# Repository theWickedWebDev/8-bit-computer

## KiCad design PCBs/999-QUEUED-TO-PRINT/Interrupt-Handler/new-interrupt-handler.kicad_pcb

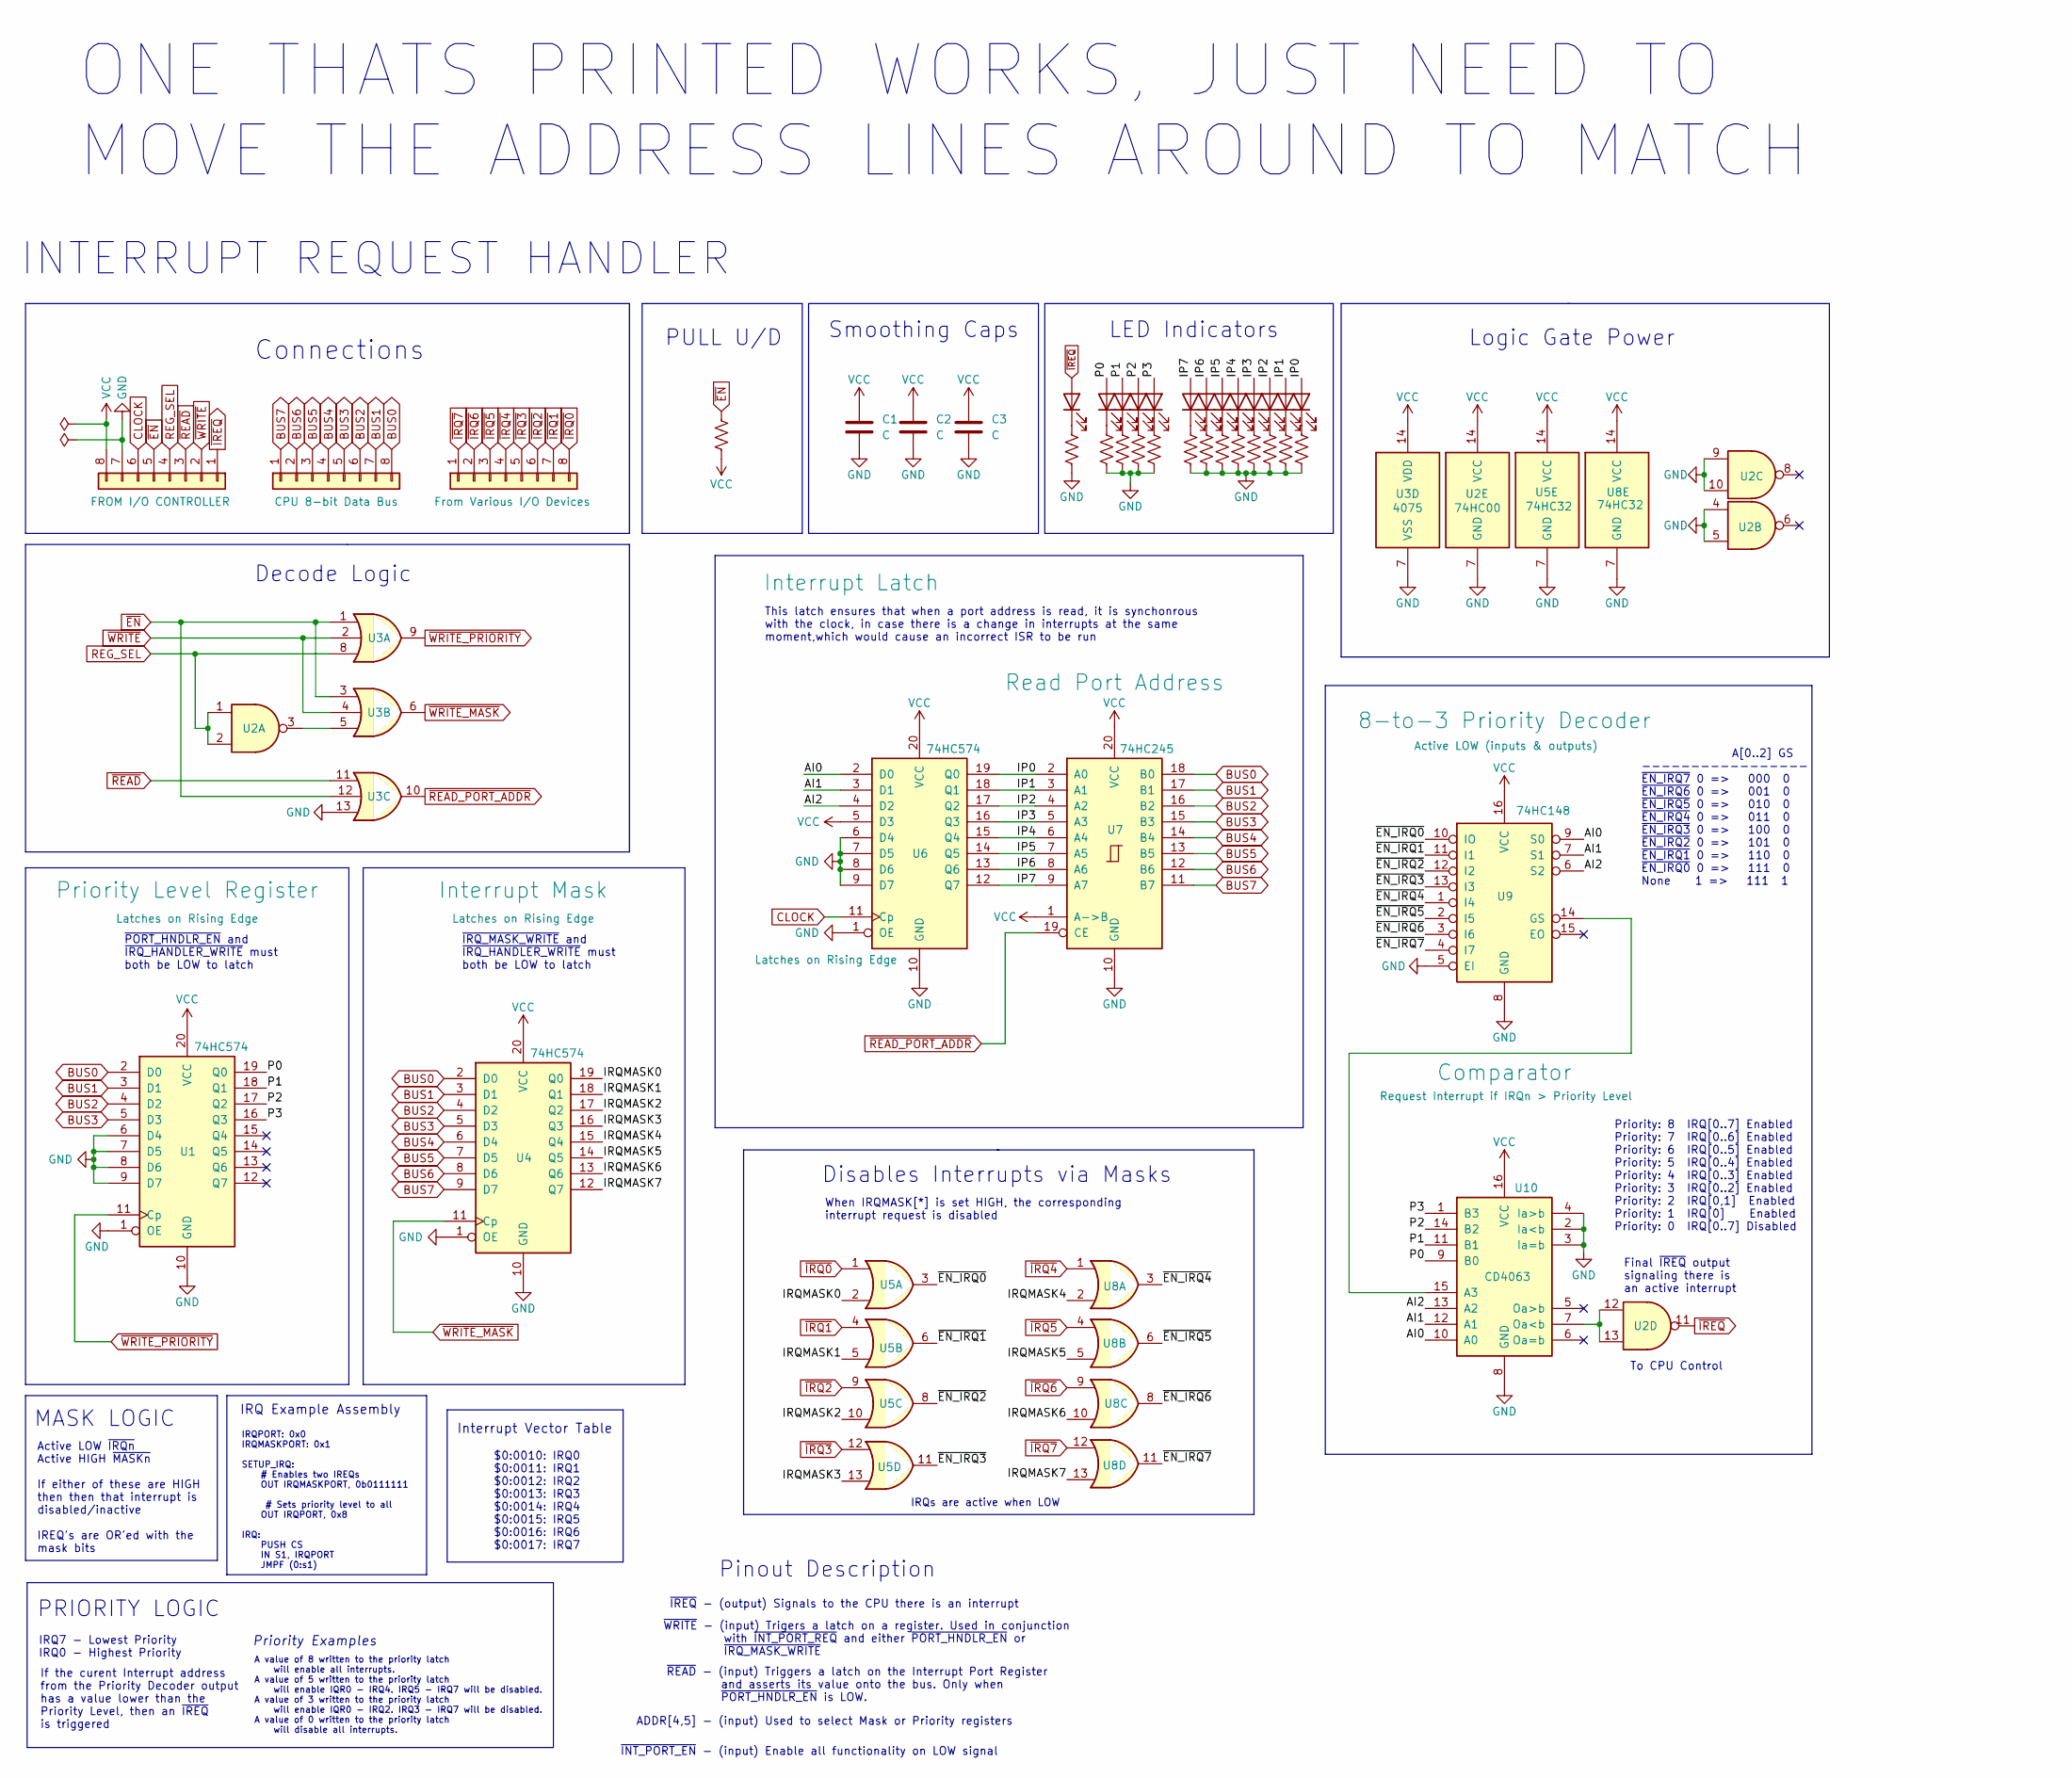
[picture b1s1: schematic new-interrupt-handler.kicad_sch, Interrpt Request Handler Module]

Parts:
C1, C2, C3: C; C_0805_2012Metric
D1, D2, D3, D4, D5, D6, D7, D8, D9, D10, D11, D12, D13: LED; LED_0805_2012Metric
J1, J2, J3: Conn_01x08; PinHeader_1x08_P2.54mm_Vertical
R1, R2, R3, R4, R5, R6, R7, R8, R9, R10, R11, R12, R13, R14: R_US; R_0805_2012Metric
U1, U4, U6: 74HC574; SO-20_5.3x12.6mm_P1.27mm
U2: 74HC00; TSSOP-14_4.4x5mm_P0.65mm
U3: 4075
U5, U8: 74HC32; TSSOP-14_4.4x5mm_P0.65mm
U7: 74HC245; TSSOP-20_4.4x6.5mm_P0.65mm
U9: 74HC148; SOIC-16_4.55x10.3mm_P1.27mm
U10: CD4063; SO-16_5.3x10.2mm_P1.27mm

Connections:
/AI0: U6.2 (D0), U9.9 (S0), U10.10 (A0)
/AI1: U6.3 (D1), U9.7 (S1), U10.12 (A1)
/AI2: U6.4 (D2), U9.6 (S2), U10.13 (A2)
/IP0: D13.2 (A), U6.19 (Q0), U7.2 (A0)
/IP1: D12.2 (A), U6.18 (Q1), U7.3 (A1)
/IP2: D11.2 (A), U6.17 (Q2), U7.4 (A2)
/IP3: D10.2 (A), U6.16 (Q3), U7.5 (A3)
/IP4: D9.2 (A), U6.15 (Q4), U7.6 (A4)
/IP5: D8.2 (A), U6.14 (Q5), U7.7 (A5)
/IP6: D7.2 (A), U6.13 (Q6), U7.8 (A6)
/IP7: D6.2 (A), U6.12 (Q7), U7.9 (A7)
/IRQMASK0: U4.19 (Q0), U5.2
/IRQMASK1: U4.18 (Q1), U5.5
/IRQMASK2: U4.17 (Q2), U5.10
/IRQMASK3: U4.16 (Q3), U5.13
/IRQMASK4: U4.15 (Q4), U8.2
/IRQMASK5: U4.14 (Q5), U8.5
/IRQMASK6: U4.13 (Q6), U8.10
/IRQMASK7: U4.12 (Q7), U8.13
/P0: D2.2 (A), U1.19 (Q0), U10.9 (B0)
/P1: D3.2 (A), U1.18 (Q1), U10.11 (B1)
/P2: D4.2 (A), U1.17 (Q2), U10.14 (B2)
/P3: D5.2 (A), U1.16 (Q3), U10.1 (B3)
/~EN_IRQ0: U5.3, U9.10 (IO)
/~EN_IRQ1: U5.6, U9.11 (I1)
/~EN_IRQ2: U5.8, U9.12 (I2)
/~EN_IRQ3: U5.11, U9.13 (I3)
/~EN_IRQ4: U8.3, U9.1 (I4)
/~EN_IRQ5: U8.6, U9.2 (I5)
/~EN_IRQ6: U8.8, U9.3 (I6)
/~EN_IRQ7: U8.11, U9.4 (I7)
BUS0: J2.8, U1.2 (D0), U4.2 (D0), U7.18 (B0)
BUS1: J2.7, U1.3 (D1), U4.3 (D1), U7.17 (B1)
BUS2: J2.6, U1.4 (D2), U4.4 (D2), U7.16 (B2)
BUS3: J2.5, U1.5 (D3), U4.5 (D3), U7.15 (B3)
BUS4: J2.4, U4.6 (D4), U7.14 (B4)
BUS5: J2.3, U4.7 (D5), U7.13 (B5)
BUS6: J2.2, U4.8 (D6), U7.12 (B6)
BUS7: J2.1, U4.9 (D7), U7.11 (B7)
CLOCK: J1.6, U6.11 (Cp)
GND: C1.2, C2.2, C3.2, J1.7, R2.2, R3.2, R4.2, R5.2, R6.2, R7.2, R8.2, R9.2, R10.2, R11.2, R12.2, R13.2, R14.2, U1.1 (OE), U1.6 (D4), U1.7 (D5), U1.8 (D6), U1.9 (D7), U1.10 (GND), U2.4, U2.5, U2.7 (GND), U2.9, U2.10, U3.7 (VSS), U3.13, U4.1 (OE), U4.10 (GND), U5.7 (GND), U6.1 (OE), U6.6 (D4), U6.7 (D5), U6.8 (D6), U6.9 (D7), U6.10 (GND), U7.10 (GND), U8.7 (GND), U9.5 (EI), U9.8 (GND), U10.2 (Ia<b), U10.3 (Ia=b), U10.4 (Ia>b), U10.8 (GND)
unnamed: D1.1 (K), R2.1
unnamed: D2.1 (K), R3.1
unnamed: D3.1 (K), R4.1
unnamed: D4.1 (K), R5.1
unnamed: D5.1 (K), R6.1
unnamed: D6.1 (K), R7.1
unnamed: D7.1 (K), R8.1
unnamed: D8.1 (K), R9.1
unnamed: D9.1 (K), R10.1
unnamed: D10.1 (K), R11.1
unnamed: D11.1 (K), R12.1
unnamed: D12.1 (K), R13.1
unnamed: D13.1 (K), R14.1
unnamed: U2.3, U3.5
unnamed: U2.12, U2.13, U10.7 (Oa<b)
unnamed: U9.14 (GS), U10.15 (A3)
REG_SEL: J1.4, U2.1, U2.2, U3.8
VCC: C1.1, C2.1, C3.1, J1.8, R1.2, U1.20 (VCC), U2.14 (VCC), U3.14 (VDD), U4.20 (VCC), U5.14 (VCC), U6.5 (D3), U6.20 (VCC), U7.1 (A->B), U7.20 (VCC), U8.14 (VCC), U9.16 (VCC), U10.16 (VCC)
~EN: J1.5, R1.1, U3.1, U3.3, U3.12
~IREQ: D1.2 (A), J1.1, U2.11
~IRQ0: J3.8, U5.1
~IRQ1: J3.7, U5.4
~IRQ2: J3.6, U5.9
~IRQ3: J3.5, U5.12
~IRQ4: J3.4, U8.1
~IRQ5: J3.3, U8.4
~IRQ6: J3.2, U8.9
~IRQ7: J3.1, U8.12
~READ_PORT_ADDR: U3.10, U7.19 (CE)
~READ: J1.3, U3.11
~WRITE_MASK: U3.6, U4.11 (Cp)
~WRITE_PRIORITY: U1.11 (Cp), U3.9
~WRITE: J1.2, U3.2, U3.4

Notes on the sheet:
When IRQMASK[*] is set HIGH, the corresponding interrupt request is disabled
Disables Interrupts via Masks
IRQPORT: 0x0 IRQMASKPORT: 0x1 SETUP_IRQ: # Enables two IREQs OUT IRQMASKPORT, 0b0111111 # Sets priority level to all OUT IRQPORT, 0x8 IRQ: PUSH CS IN S1, IRQPORT JMPF (0:s1)
ONE THATS PRINTED WORKS, JUST NEED TO MOVE THE ADDRESS LINES AROUND TO MATCH
~{IRQ_MASK_WRITE} and ~{IRQ_HANDLER_WRITE} must both be LOW to latch
A[0..2] GS ----------------- ~{EN_IRQ7} 0 => 000 0 ~{EN_IRQ6} 0 => 001 0 ~{EN_IRQ5} 0 => 010 0 ~{EN_IRQ4} 0 => 011 0 ~{EN_IRQ3} 0 => 100 0 ~{EN_IRQ2} 0 => 101 0 ~{EN_IRQ1} 0 => 110 0 ~{EN_IRQ0} 0 => 111 0 None 1 => 111 1
Priority: 8 IRQ[0..7] Enabled Priority: 7 IRQ[0..6] Enabled Priority: 6 IRQ[0..5] Enabled Priority: 5 IRQ[0..4] Enabled Priority: 4 IRQ[0..3] Enabled Priority: 3 IRQ[0..2] Enabled Priority: 2 IRQ[0,1] Enabled Priority: 1 IRQ[0] Enabled Priority: 0 IRQ[0..7] Disabled
INTERRUPT REQUEST HANDLER
~{INT_PORT_EN} - (input) Enable all functionality on LOW signal
Pinout Description
LED Indicators
To CPU Control
IRQs are active when LOW
PULL U/D
$0:0010: IRQ0 $0:0011: IRQ1 $0:0012: IRQ2 $0:0013: IRQ3 $0:0014: IRQ4 $0:0015: IRQ5 $0:0016: IRQ6 $0:0017: IRQ7
~{WRITE} - (input) Trigers a latch on a register. Used in conjunction with ~{INT_PORT_REQ} and either ~{PORT_HNDLR_EN} or ~{IRQ_MASK_WRITE}
Logic Gate Power
~{IREQ} - (output) Signals to the CPU there is an interrupt
IRQ7 - Lowest Priority IRQ0 - Highest Priority
If the curent Interrupt address from the Priority Decoder output has a value lower than the Priority Level, then an ~{IREQ} is triggered
A value of 8 written to the priority latch will enable all interrupts. A value of 5 written to the priority latch will enable IQR0 - IRQ4. IRQ5 - IRQ7 will be disabled. A value of 3 written to the priority latch will enable IQR0 - IRQ2. IRQ3 - IRQ7 will be disabled. A value of 0 written to the prio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
Active LOW ~{IRQn} Active HIGH ~{MASKn} If either of these are HIGH then then that interrupt is disabled/inactive IREQ's are OR'ed with the mask bits
ADDR[4,5] - (input) Used to select Mask or Priority registers
MASK LOGIC
This latch ensures that when a port address is read, it is synchonrous with the clock, in case there is a change in interrupts at the same moment,which would cause an incorrect ISR to be run
Smoothing Caps
IRQ Example Assembly
Final ~{IREQ} output signaling there is an active interrupt
Priority Examples
~{PORT_HNDLR_EN} and ~{IRQ_HANDLER_WRITE} must both be LOW to latch
PRIORITY LOGIC
Decode Logic
~{READ} - (input) Triggers a latch on the Interrupt Port Register and asserts its value onto the bus. Only when ~{PORT_HNDLR_EN} is LOW.
Connections
Interrupt Vector Table

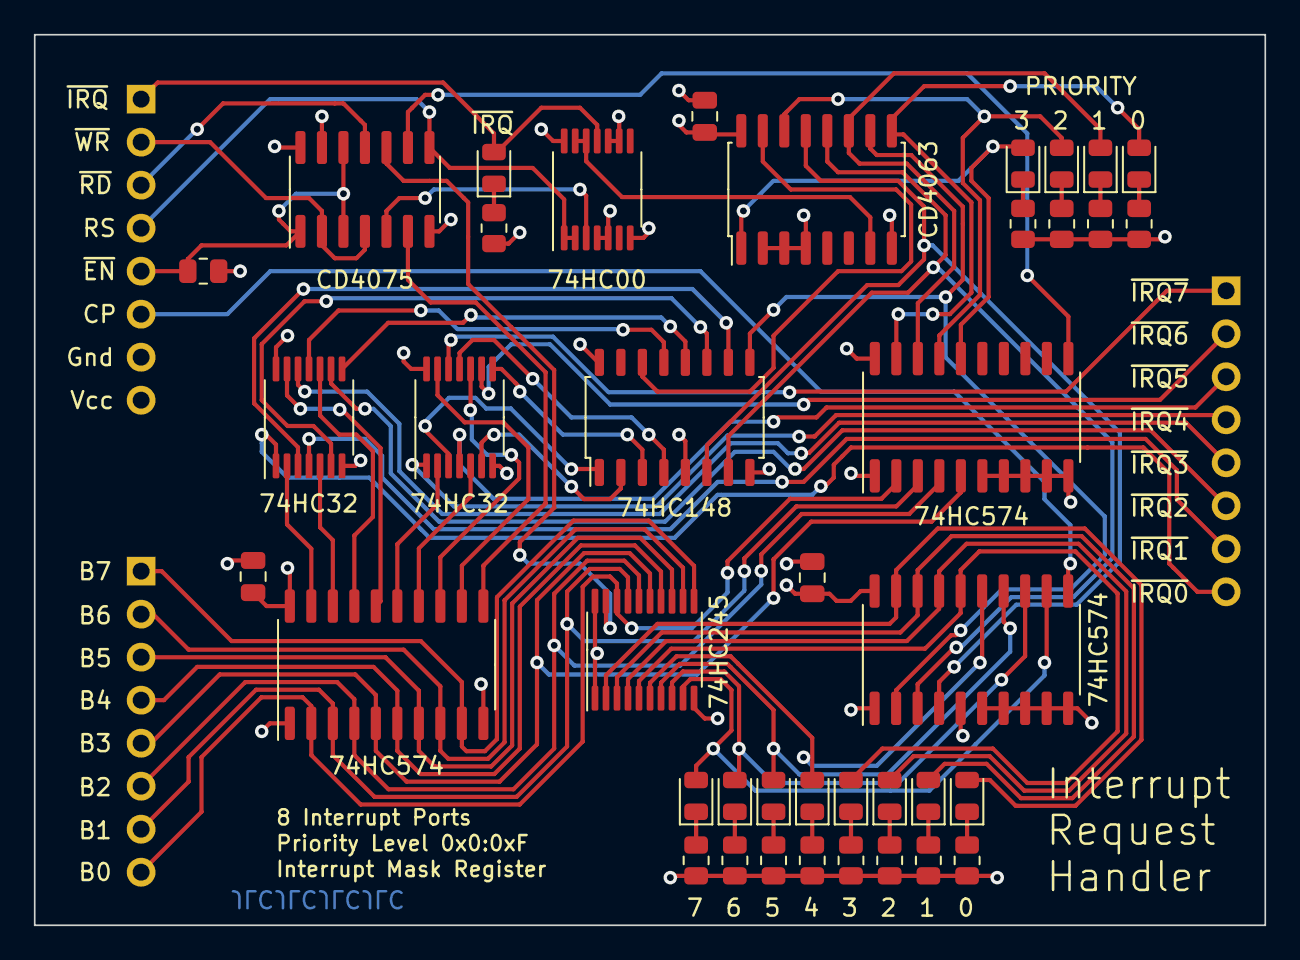
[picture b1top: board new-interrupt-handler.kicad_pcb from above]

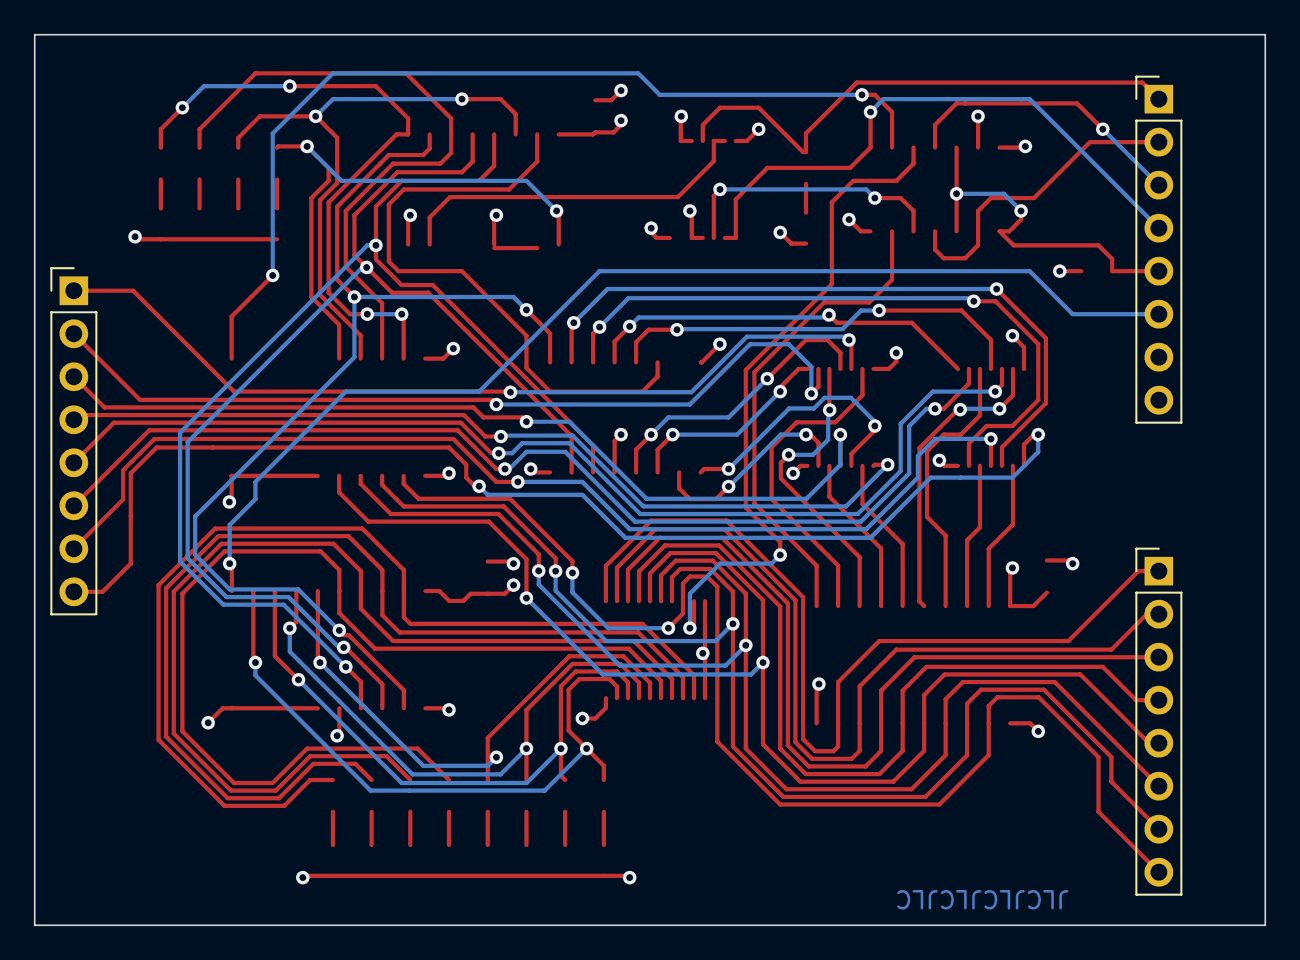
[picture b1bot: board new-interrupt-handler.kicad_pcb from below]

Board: 4 copper layers, 72.7 x 52.6 mm, 43 parts (3 on the bottom side), 74 nets.

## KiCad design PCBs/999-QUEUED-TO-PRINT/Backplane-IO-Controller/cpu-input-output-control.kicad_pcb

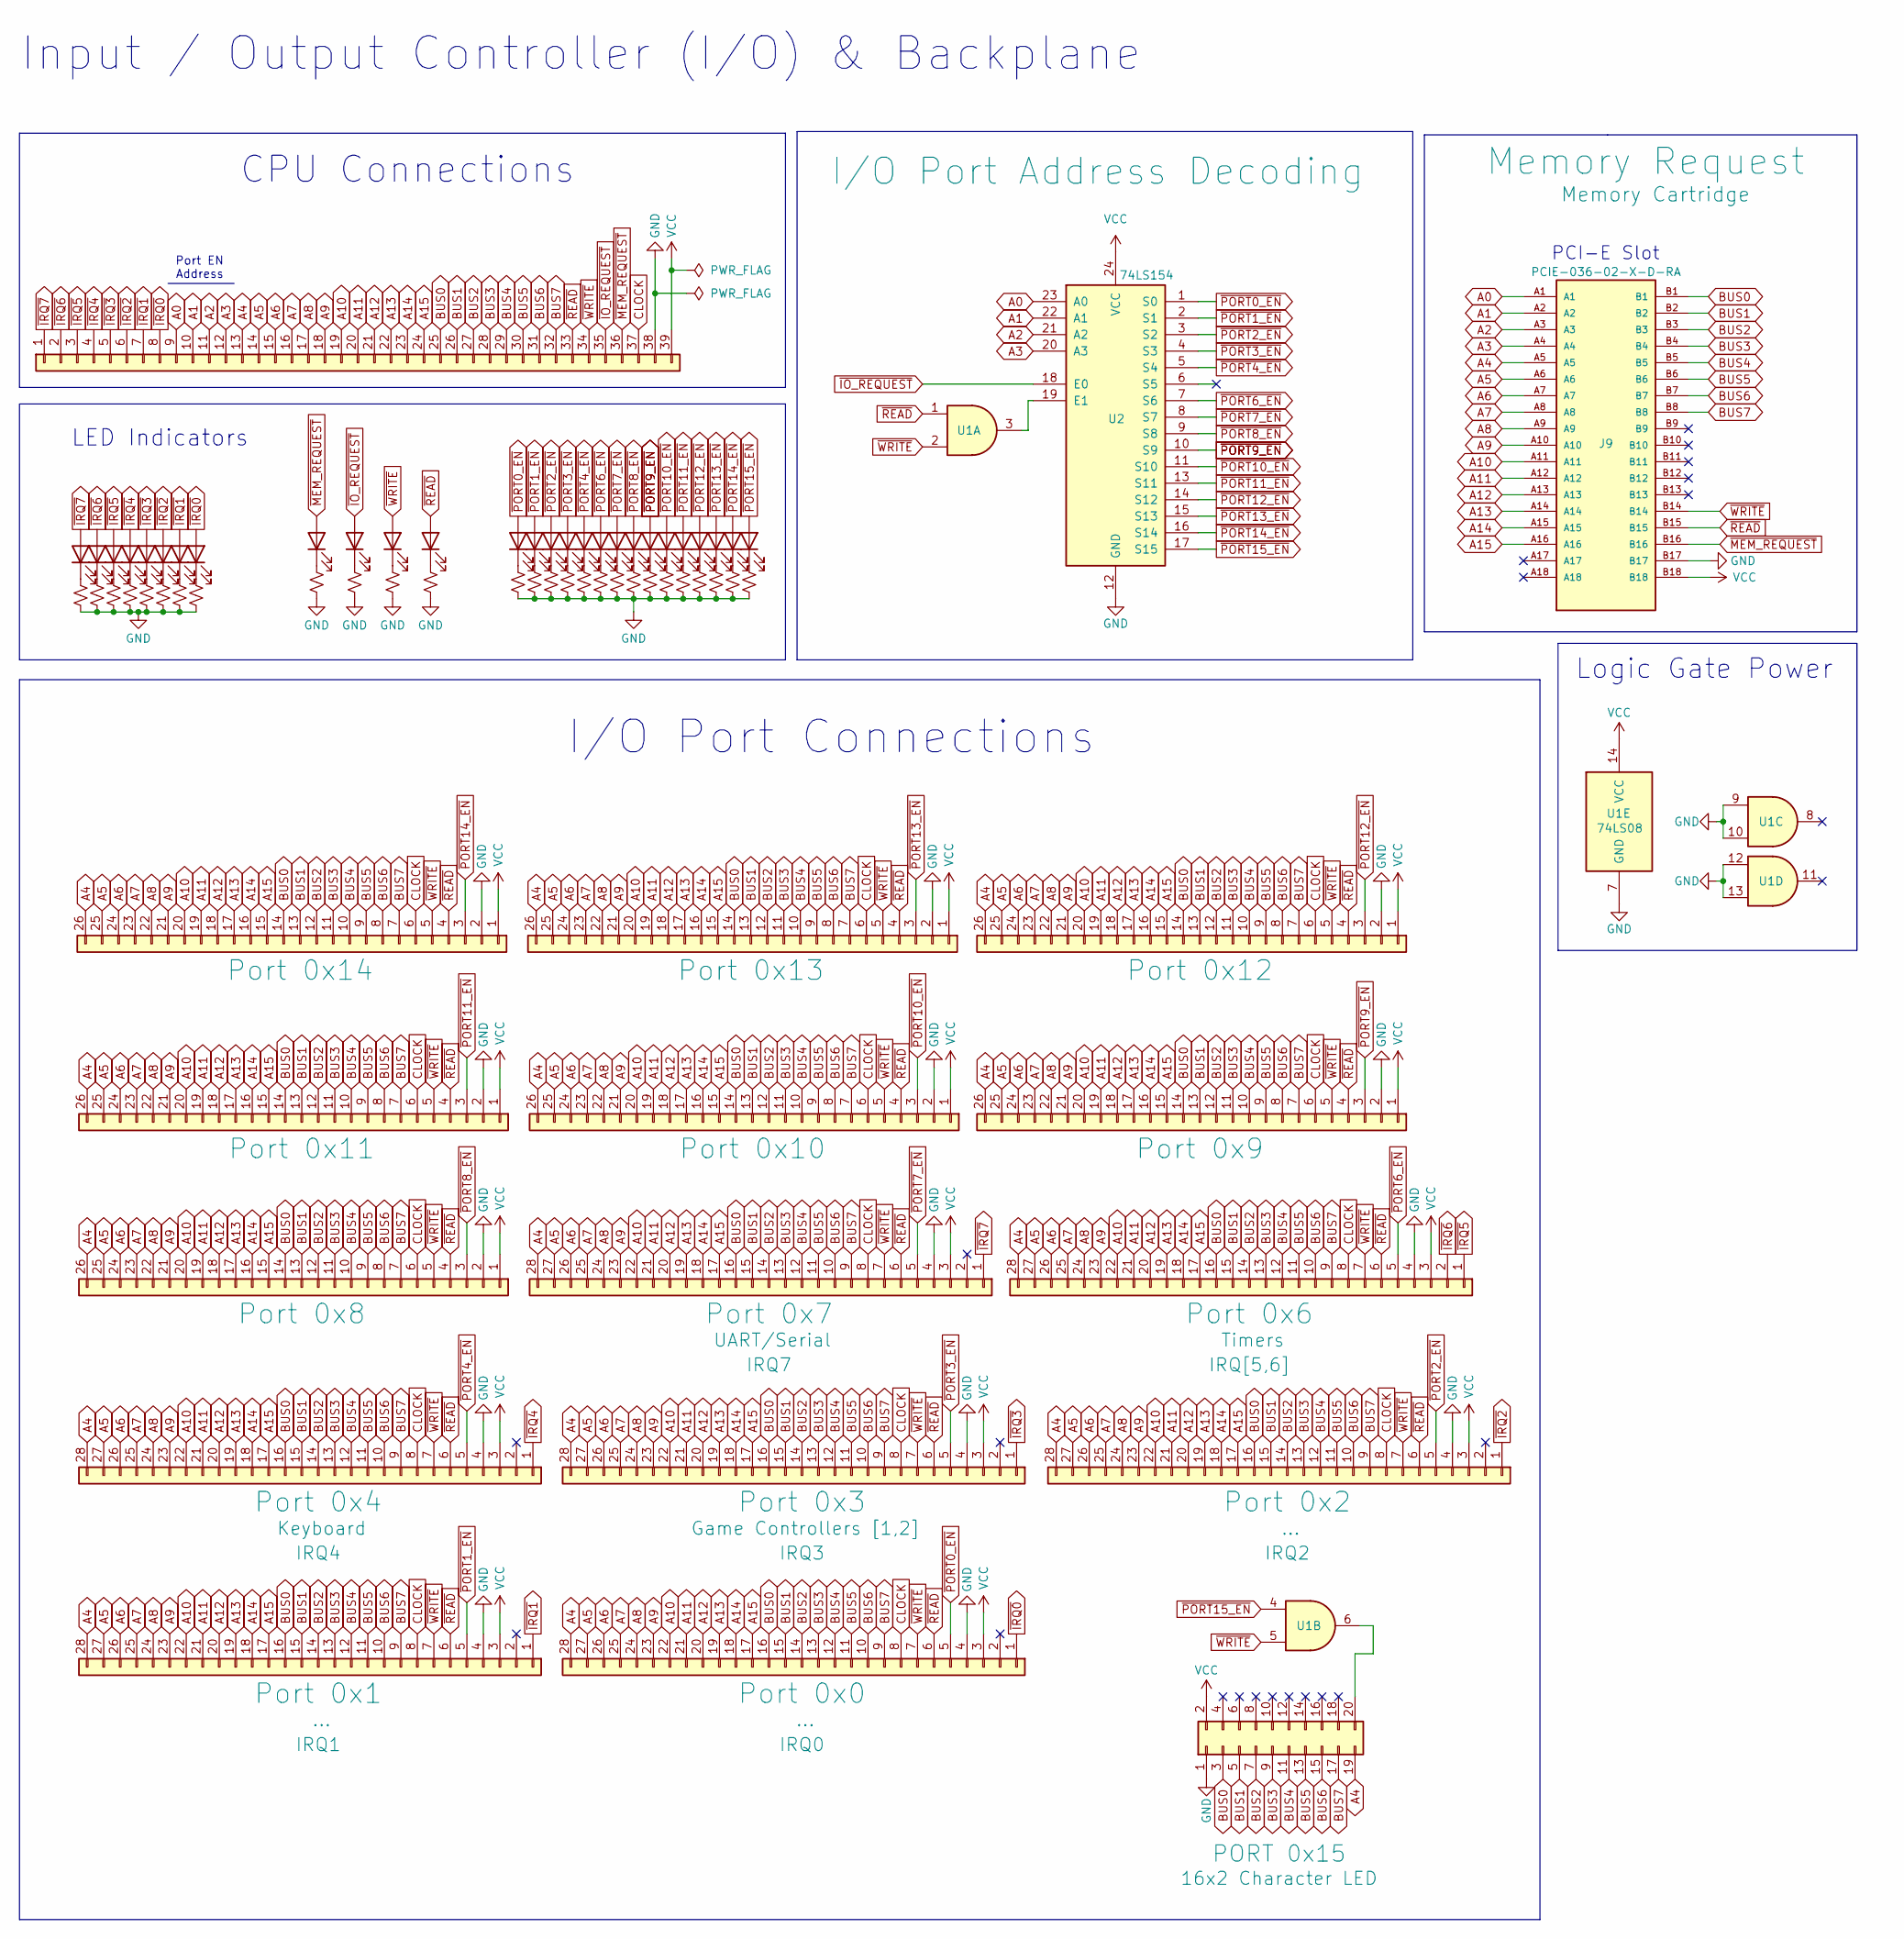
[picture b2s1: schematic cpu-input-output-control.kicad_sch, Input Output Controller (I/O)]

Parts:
D1, D2, D3, D4, D5, D6, D7, D8, D9, D10, D11, D12, D13, D14, D15, D16, D17, D18, D19, D20, D21, D22, D23, D24, D25, D26, D27: LED; LED_0805_2012Metric
J1, J4, J6, J8, J12, J14, J16: Conn_01x26; PinSocket_1x26_P2.54mm_Vertical
J2, J5, J7, J10, J13, J15, J17: Conn_01x28; PinSocket_1x28_P2.54mm_Vertical
J3: Conn_01x39; PinSocket_1x39_P2.54mm_Horizontal
J9: PCIE-036-02-X-D-RA; SAMTEC_PCIE-036-02-X-D-RA; PARTREV D
J11: Conn_02x20_Odd_Even; IDC-Header_2x10_P2.54mm_Vertical
R1, R2, R3, R4, R5, R6, R7, R8, R9, R10, R11, R12, R13, R14, R15, R16, R17, R18, R19, R20, R21, R22, R23, R24, R25, R26, R27: R_Small_US; R_0805_2012Metric
U1: 74LS08; SOIC-14_3.9x8.7mm_P1.27mm
U2: 74LS154; SO-24_5.3x15mm_P1.27mm

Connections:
A0: J3.9, J9.A1, U2.23 (A0)
A1: J3.10, J9.A2, U2.22 (A1)
A2: J3.11, J9.A3, U2.21 (A2)
A3: J3.12, J9.A4, U2.20 (A3)
A4: J1.26, J2.28, J3.13, J4.26, J5.28, J6.26, J7.28, J8.26, J9.A5, J10.28, J11.19, J12.26, J13.28, J14.26, J15.28, J16.26, J17.28
A5: J1.25, J2.27, J3.14, J4.25, J5.27, J6.25, J7.27, J8.25, J9.A6, J10.27, J12.25, J13.27, J14.25, J15.27, J16.25, J17.27
A6: J1.24, J2.26, J3.15, J4.24, J5.26, J6.24, J7.26, J8.24, J9.A7, J10.26, J12.24, J13.26, J14.24, J15.26, J16.24, J17.26
A7: J1.23, J2.25, J3.16, J4.23, J5.25, J6.23, J7.25, J8.23, J9.A8, J10.25, J12.23, J13.25, J14.23, J15.25, J16.23, J17.25
A8: J1.22, J2.24, J3.17, J4.22, J5.24, J6.22, J7.24, J8.22, J9.A9, J10.24, J12.22, J13.24, J14.22, J15.24, J16.22, J17.24
A9: J1.21, J2.23, J3.18, J4.21, J5.23, J6.21, J7.23, J8.21, J9.A10, J10.23, J12.21, J13.23, J14.21, J15.23, J16.21, J17.23
A10: J1.20, J2.22, J3.19, J4.20, J5.22, J6.20, J7.22, J8.20, J9.A11, J10.22, J12.20, J13.22, J14.20, J15.22, J16.20, J17.22
A11: J1.19, J2.21, J3.20, J4.19, J5.21, J6.19, J7.21, J8.19, J9.A12, J10.21, J12.19, J13.21, J14.19, J15.21, J16.19, J17.21
A12: J1.18, J2.20, J3.21, J4.18, J5.20, J6.18, J7.20, J8.18, J9.A13, J10.20, J12.18, J13.20, J14.18, J15.20, J16.18, J17.20
A13: J1.17, J2.19, J3.22, J4.17, J5.19, J6.17, J7.19, J8.17, J9.A14, J10.19, J12.17, J13.19, J14.17, J15.19, J16.17, J17.19
A14: J1.16, J2.18, J3.23, J4.16, J5.18, J6.16, J7.18, J8.16, J9.A15, J10.18, J12.16, J13.18, J14.16, J15.18, J16.16, J17.18
A15: J1.15, J2.17, J3.24, J4.15, J5.17, J6.15, J7.17, J8.15, J9.A16, J10.17, J12.15, J13.17, J14.15, J15.17, J16.15, J17.17
BUS0: J1.14, J2.16, J3.25, J4.14, J5.16, J6.14, J7.16, J8.14, J9.B1, J10.16, J11.3, J12.14, J13.16, J14.14, J15.16, J16.14, J17.16
BUS1: J1.13, J2.15, J3.26, J4.13, J5.15, J6.13, J7.15, J8.13, J9.B2, J10.15, J11.5, J12.13, J13.15, J14.13, J15.15, J16.13, J17.15
BUS2: J1.12, J2.14, J3.27, J4.12, J5.14, J6.12, J7.14, J8.12, J9.B3, J10.14, J11.7, J12.12, J13.14, J14.12, J15.14, J16.12, J17.14
BUS3: J1.11, J2.13, J3.28, J4.11, J5.13, J6.11, J7.13, J8.11, J9.B4, J10.13, J11.9, J12.11, J13.13, J14.11, J15.13, J16.11, J17.13
BUS4: J1.10, J2.12, J3.29, J4.10, J5.12, J6.10, J7.12, J8.10, J9.B5, J10.12, J11.11, J12.10, J13.12, J14.10, J15.12, J16.10, J17.12
BUS5: J1.9, J2.11, J3.30, J4.9, J5.11, J6.9, J7.11, J8.9, J9.B6, J10.11, J11.13, J12.9, J13.11, J14.9, J15.11, J16.9, J17.11
BUS6: J1.8, J2.10, J3.31, J4.8, J5.10, J6.8, J7.10, J8.8, J9.B7, J10.10, J11.15, J12.8, J13.10, J14.8, J15.10, J16.8, J17.10
BUS7: J1.7, J2.9, J3.32, J4.7, J5.9, J6.7, J7.9, J8.7, J9.B8, J10.9, J11.17, J12.7, J13.9, J14.7, J15.9, J16.7, J17.9
CLOCK: J1.6, J2.8, J3.37, J4.6, J5.8, J6.6, J7.8, J8.6, J10.8, J12.6, J13.8, J14.6, J15.8, J16.6, J17.8
GND: J1.2, J2.4, J3.38, J4.2, J5.4, J6.2, J7.4, J8.2, J9.B17, J10.4, J11.1, J12.2, J13.4, J14.2, J15.4, J16.2, J17.4, R1.2, R2.2, R3.2, R4.2, R5.2, R6.2, R7.2, R8.2, R9.2, R10.2, R11.2, R12.2, R13.2, R14.2, R15.2, R16.2, R17.2, R18.2, R19.2, R20.2, R21.2, R22.2, R23.2, R24.2, R25.2, R26.2, R27.2, U1.7 (GND), U1.9, U1.10, U1.12, U1.13, U2.12 (GND)
unnamed: D1.1 (K), R1.1
unnamed: D2.1 (K), R2.1
unnamed: D3.1 (K), R3.1
unnamed: D4.1 (K), R4.1
unnamed: D5.1 (K), R5.1
unnamed: D6.1 (K), R6.1
unnamed: D7.1 (K), R7.1
unnamed: D8.1 (K), R8.1
unnamed: D9.1 (K), R9.1
unnamed: D10.1 (K), R10.1
unnamed: D11.1 (K), R11.1
unnamed: D12.1 (K), R12.1
unnamed: D13.1 (K), R13.1
unnamed: D14.1 (K), R14.1
unnamed: D15.1 (K), R15.1
unnamed: D16.1 (K), R16.1
unnamed: D17.1 (K), R17.1
unnamed: D18.1 (K), R18.1
unnamed: D19.1 (K), R19.1
unnamed: D20.1 (K), R20.1
unnamed: D21.1 (K), R21.1
unnamed: D22.1 (K), R22.1
unnamed: D23.1 (K), R23.1
unnamed: D24.1 (K), R24.1
unnamed: D25.1 (K), R25.1
unnamed: D26.1 (K), R26.1
unnamed: D27.1 (K), R27.1
unnamed: J11.20, U1.6
unnamed: U1.3, U2.19 (E1)
VCC: J1.1, J2.3, J3.39, J4.1, J5.3, J6.1, J7.3, J8.1, J9.B18, J10.3, J11.2, J12.1, J13.3, J14.1, J15.3, J16.1, J17.3, U1.14 (VCC), U2.24 (VCC)
~IO_REQUEST: D10.2 (A), J3.35, U2.18 (E0)
~IRQ0: D8.2 (A), J3.8, J17.1
~IRQ1: D7.2 (A), J3.7, J15.1
~IRQ2: D6.2 (A), J3.6, J13.1
~IRQ3: D5.2 (A), J3.5, J10.1
~IRQ4: D4.2 (A), J3.4, J7.1
~IRQ5: D3.2 (A), J3.3, J5.1
~IRQ6: D2.2 (A), J3.2, J5.2
~IRQ7: D1.2 (A), J2.1, J3.1
~MEM_REQUEST: D9.2 (A), J3.36, J9.B16
~PORT0_EN: D13.2 (A), J17.5, U2.1 (S0)
~PORT1_EN: D14.2 (A), J15.5, U2.2 (S1)
~PORT2_EN: D15.2 (A), J13.5, U2.3 (S2)
~PORT3_EN: D16.2 (A), J10.5, U2.4 (S3)
~PORT4_EN: D17.2 (A), J7.5, U2.5 (S4)
~PORT6_EN: D18.2 (A), J5.5, U2.7 (S6)
~PORT7_EN: D19.2 (A), J2.5, U2.8 (S7)
~PORT8_EN: D20.2 (A), J16.3, U2.9 (S8)
~PORT9_EN: D21.2 (A), J14.3, U2.10 (S9)
~PORT10_EN: D22.2 (A), J12.3, U2.11 (S10)
~PORT11_EN: D23.2 (A), J8.3, U2.13 (S11)
~PORT12_EN: D24.2 (A), J6.3, U2.14 (S12)
~PORT13_EN: D25.2 (A), J4.3, U2.15 (S13)
~PORT14_EN: D26.2 (A), J1.3, U2.16 (S14)
~PORT15_EN: D27.2 (A), U1.4, U2.17 (S15)
~READ: D12.2 (A), J1.4, J2.6, J3.33, J4.4, J5.6, J6.4, J7.6, J8.4, J9.B15, J10.6, J12.4, J13.6, J14.4, J15.6, J16.4, J17.6, U1.1
~WRITE: D11.2 (A), J1.5, J2.7, J3.34, J4.5, J5.7, J6.5, J7.7, J8.5, J9.B14, J10.7, J12.5, J13.7, J14.5, J15.7, J16.5, J17.7, U1.2, U1.5

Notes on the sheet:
CPU Connections
Logic Gate Power
Input / Output Controller (I/O) & Backplane
PCI-E Slot
Port EN Address
LED Indicators
I/O Port Connections

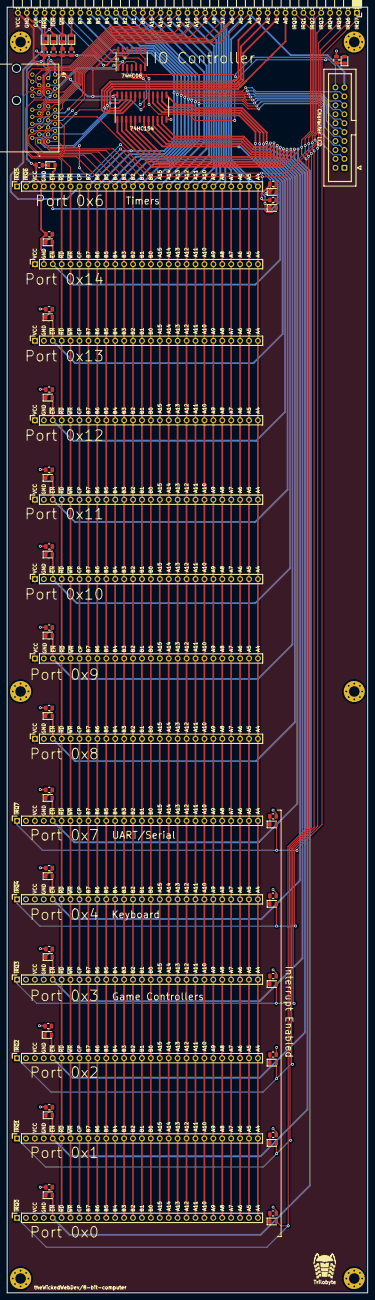
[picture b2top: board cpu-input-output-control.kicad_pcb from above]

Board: 2 copper layers, 102.6 x 366.0 mm, 73 parts (0 on the bottom side), 83 nets.

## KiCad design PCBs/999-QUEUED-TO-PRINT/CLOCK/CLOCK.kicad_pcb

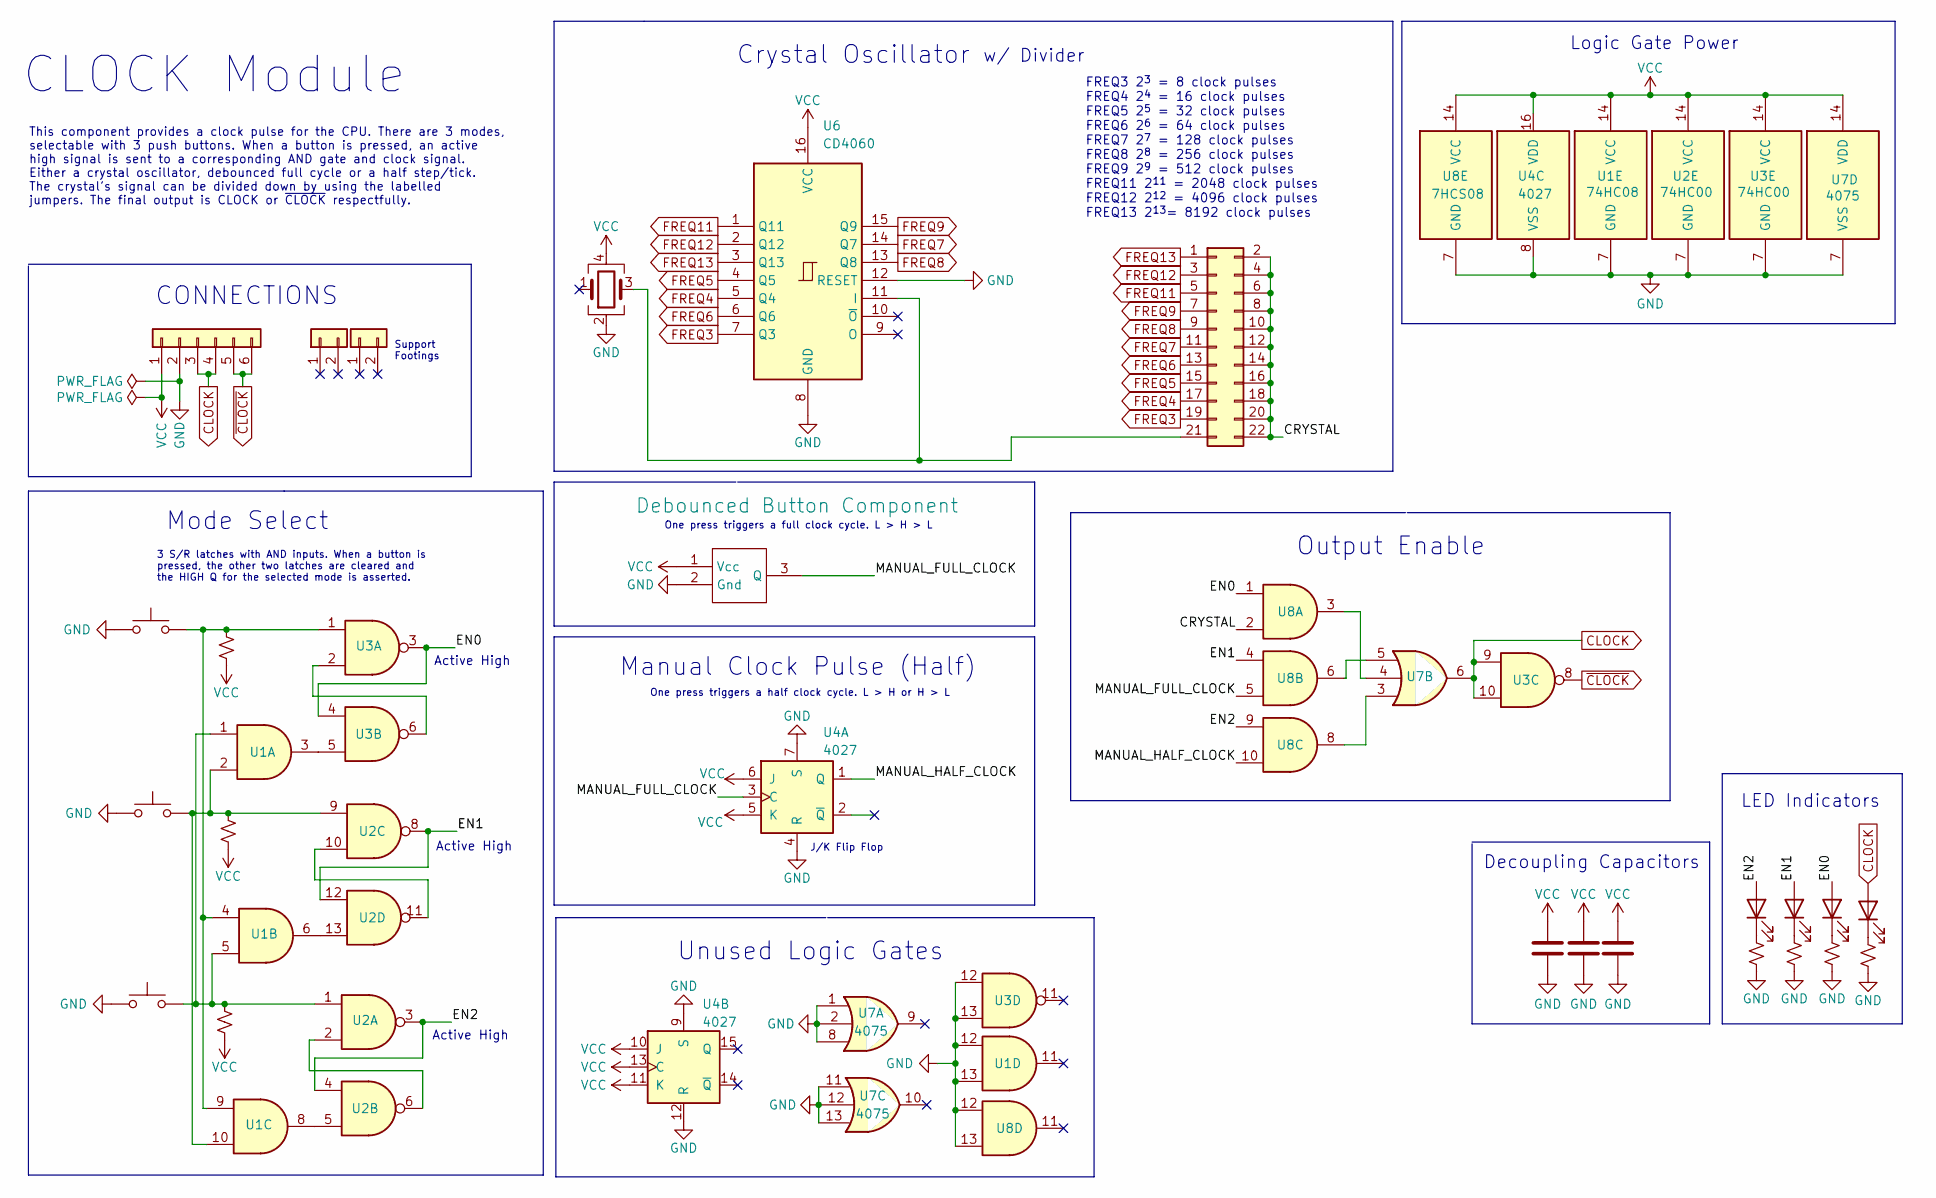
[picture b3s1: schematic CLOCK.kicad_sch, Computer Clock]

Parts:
C1, C2, C3: C; C_0805_2012Metric
D1, D2, D3, D4: LED; LED_0805_2012Metric
J1: Conn_01x06; PinHeader_1x06_P2.54mm_Vertical
J2, J3: Conn_01x02; PinHeader_1x02_P2.54mm_Vertical
J4: Conn_02x11_Odd_Even; PinHeader_2x11_P2.54mm_Vertical
R1, R2, R3, R4, R5, R6, R7: R_Small_US; R_0805_2012Metric
SW1, SW2, SW3: SW_Push; SW_PUSH_6mm
U1: 74HC08; SOIC-14_3.9x8.7mm_P1.27mm
U2, U3: 74HC00; SOIC-14_3.9x8.7mm_P1.27mm
U4: 4027
U5: DebouncedButton; breakout-debounce-btn
U6: CD4060; SOIC-16W_5.3x10.2mm_P1.27mm
U7: 4075; SOIC-14_3.9x8.7mm_P1.27mm
U8: 7HCS08; SOIC-14_3.9x8.7mm_P1.27mm
Y1: Crystal_GND24; Crystal_DIP_4_14

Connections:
/CRYSTAL: J4.2, J4.4, J4.6, J4.8, J4.10, J4.12, J4.14, J4.16, J4.18, J4.20, J4.22, U8.2
/EN0: D3.2 (A), U3.3, U3.4, U8.1
/EN1: D2.2 (A), U2.8, U2.12, U8.4
/EN2: D1.2 (A), U2.3, U2.4, U8.9
/MANUAL_FULL_CLOCK: U4.3 (C), U5.3 (Q), U8.5; also elsewhere on the board
/MANUAL_HALF_CLOCK: U4.1 (Q), U8.10
CLOCK: D4.2 (A), J1.3, J1.4, U3.9, U3.10, U7.6
FREQ3: J4.19, U6.7 (Q3)
FREQ4: J4.17, U6.5 (Q4)
FREQ5: J4.15, U6.4 (Q5)
FREQ6: J4.13, U6.6 (Q6)
FREQ7: J4.11, U6.14 (Q7)
FREQ8: J4.9, U6.13 (Q8)
FREQ9: J4.7, U6.15 (Q9)
FREQ11: J4.5, U6.1 (Q11)
FREQ12: J4.3, U6.2 (Q12)
FREQ13: J4.1, U6.3 (Q13)
GND: C1.2, C2.2, C3.2, J1.2, R4.1, R5.1, R6.1, R7.1, SW1.1, SW2.1, SW3.1, U1.7 (GND), U1.12, U1.13, U2.7 (GND), U3.7 (GND), U3.12, U3.13, U4.4 (R), U4.7 (S), U4.8 (VSS), U4.9 (S), U4.12 (R), U5.2 (Gnd), U6.8 (GND), U6.12 (RESET), U7.1, U7.2, U7.7 (VSS), U7.8, U7.11, U7.12, U7.13, U8.7 (GND), U8.12, U8.13, Y1.2; also elsewhere on the board
unnamed: D1.1 (K), R4.2
unnamed: D2.1 (K), R5.2
unnamed: D3.1 (K), R6.2
unnamed: D4.1 (K), R7.2
unnamed: J4.21, U6.11 (I), Y1.3
unnamed: R1.2, SW1.2, U1.1, U1.5, U2.1
unnamed: R2.2, SW2.2, U1.4, U1.9, U3.1
unnamed: R3.2, SW3.2, U1.2, U1.10, U2.9
unnamed: U1.3, U3.5
unnamed: U1.6, U2.13
unnamed: U1.8, U2.5
unnamed: U2.2, U2.6
unnamed: U2.10, U2.11
unnamed: U3.2, U3.6
unnamed: U7.3, U8.8
unnamed: U7.4, U8.3
unnamed: U7.5, U8.6
VCC: C1.1, C2.1, C3.1, J1.1, R1.1, R2.1, R3.1, U1.14 (VCC), U2.14 (VCC), U3.14 (VCC), U4.5 (K), U4.6 (J), U4.10 (J), U4.11 (K), U4.13 (C), U4.16 (VDD), U5.1 (Vcc), U6.16 (VCC), U7.14 (VDD), U8.14 (VCC), Y1.4; also elsewhere on the board
~CLOCK: J1.5, J1.6, U3.8

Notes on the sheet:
3 S/R latches with AND inputs. When a button is pressed, the other two latches are cleared and the HIGH Q for the selected mode is asserted.
Output Enable
Active High
Decoupling Capacitors
One press triggers a full clock cycle. L > H > L
J/K Flip Flop
LED Indicators
CONNECTIONS
This component provides a clock pulse for the CPU. There are 3 modes, selectable with 3 push buttons. When a button is pressed, an active high signal is sent to a corresponding AND gate and clock signal. Either a crystal oscillator, debounced full cycle or a half step/tick. The crystal's signal can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
Crystal Oscillator
Manual Clock Pulse (Half)
Mode Select
Logic Gate Power
w/ Divider
Support Footings
One press triggers a half clock cycle. L > H or H > L
Unused Logic Gates
CLOCK Module
FREQ3 2^{3} = 8 clock pulses FREQ4 2^{4} = 16 clock pulses FREQ5 2^{5} = 32 clock pulses FREQ6 2^{6} = 64 clock pulses FREQ7 2^{7} = 128 clock pulses FREQ8 2^{8} = 256 clock pulses FREQ9 2^{9} = 512 clock pulses FREQ11 2^{11} = 2048 clock pulses FREQ12 2^{12} = 4096 clock pulses FREQ13 2^{13}= 8192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
